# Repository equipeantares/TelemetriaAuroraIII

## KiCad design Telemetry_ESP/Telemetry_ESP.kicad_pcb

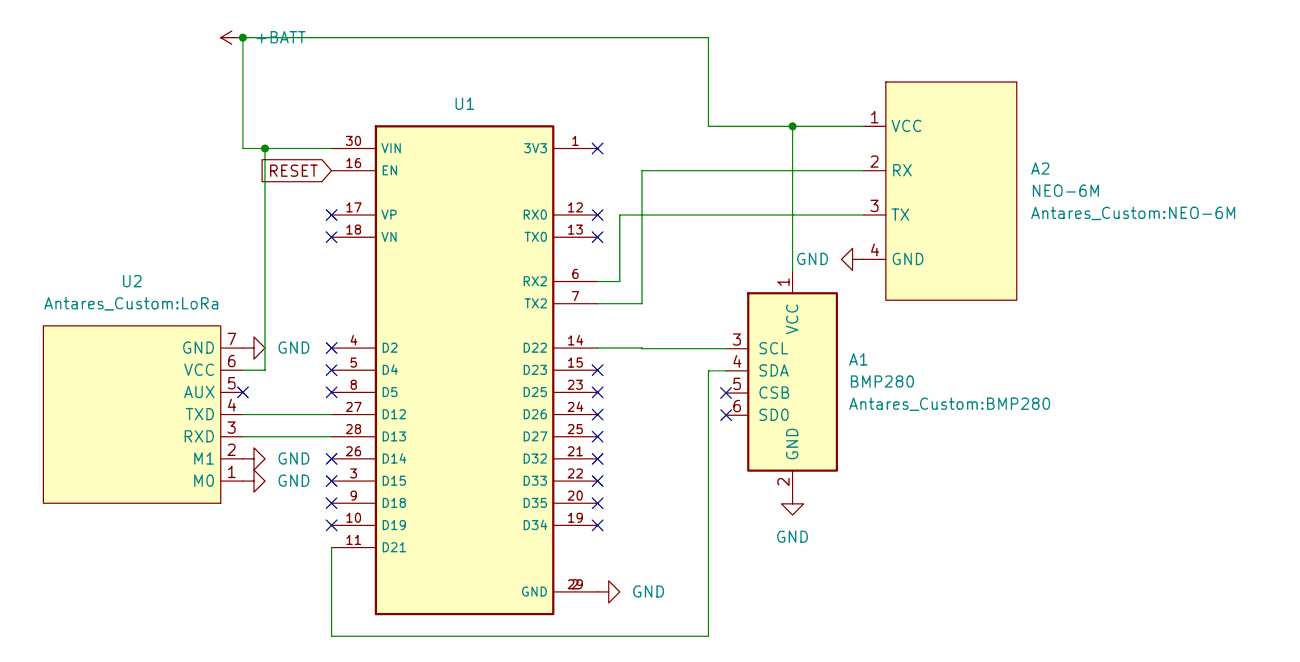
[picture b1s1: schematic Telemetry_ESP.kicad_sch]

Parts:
A1: BMP280
A2: NEO-6M
U1: MODULE_ESP32_DEVKIT_V1
U2: LoRa

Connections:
+BATT: A1.1 (VCC), A2.1 (VCC), U1.30 (VIN), U2.6 (VCC)
GND: A1.2 (GND), A2.4 (GND), U1.2 (GND), U1.29 (GND), U2.1 (M0), U2.2 (M1), U2.7 (GND)
unnamed: A1.3 (SCL), U1.14 (D22)
unnamed: A1.4 (SDA), U1.11 (D21)
unnamed: A2.2 (RX), U1.7 (TX2)
unnamed: A2.3 (TX), U1.6 (RX2)
unnamed: U1.27 (D12), U2.4 (TXD)
unnamed: U1.28 (D13), U2.3 (RXD)
RESET: U1.16 (EN)

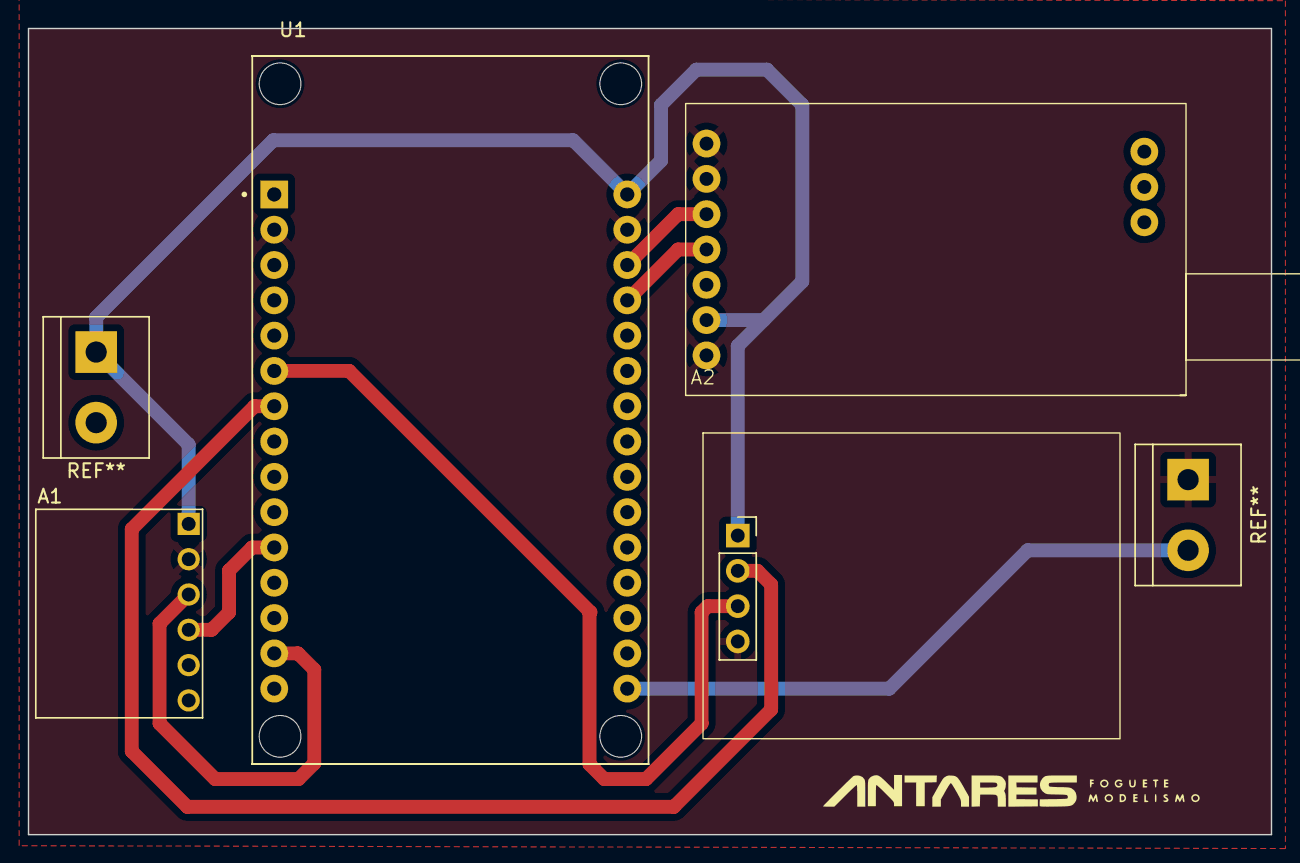
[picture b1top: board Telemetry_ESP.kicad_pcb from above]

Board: 2 copper layers, 89.4 x 58.0 mm, 4 parts (0 on the bottom side), 8 nets.

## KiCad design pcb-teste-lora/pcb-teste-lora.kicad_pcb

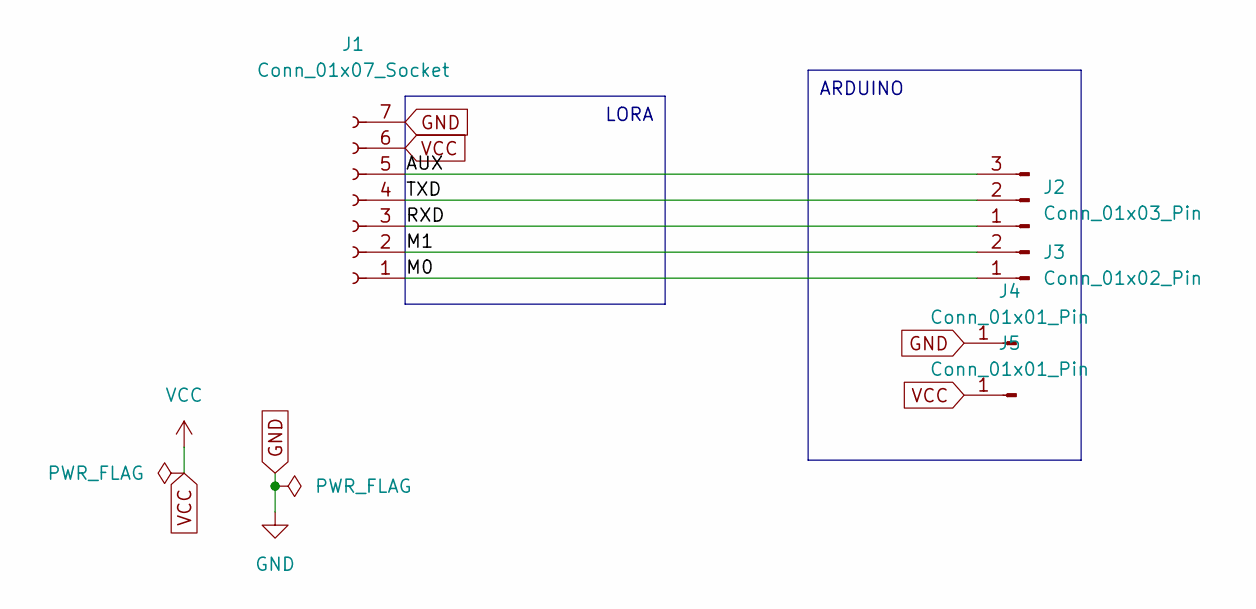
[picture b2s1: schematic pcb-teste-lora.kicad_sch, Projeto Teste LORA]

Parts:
J1: Conn_01x07_Socket; PinSocket_1x07_P2.54mm_Vertical
J2: Conn_01x03_Pin; PinSocket_1x03_P2.54mm_Vertical
J3: Conn_01x02_Pin; PinSocket_1x02_P2.54mm_Vertical
J4, J5: Conn_01x01_Pin; PinSocket_1x01_P2.00mm_Vertical

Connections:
/AUX: J1.5, J2.3
/M0: J1.1, J3.1
/M1: J1.2, J3.2
/RXD: J1.3, J2.1
/TXD: J1.4, J2.2
GND: J1.7, J4.1
VCC: J1.6, J5.1

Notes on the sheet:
LORA
ARDUINO

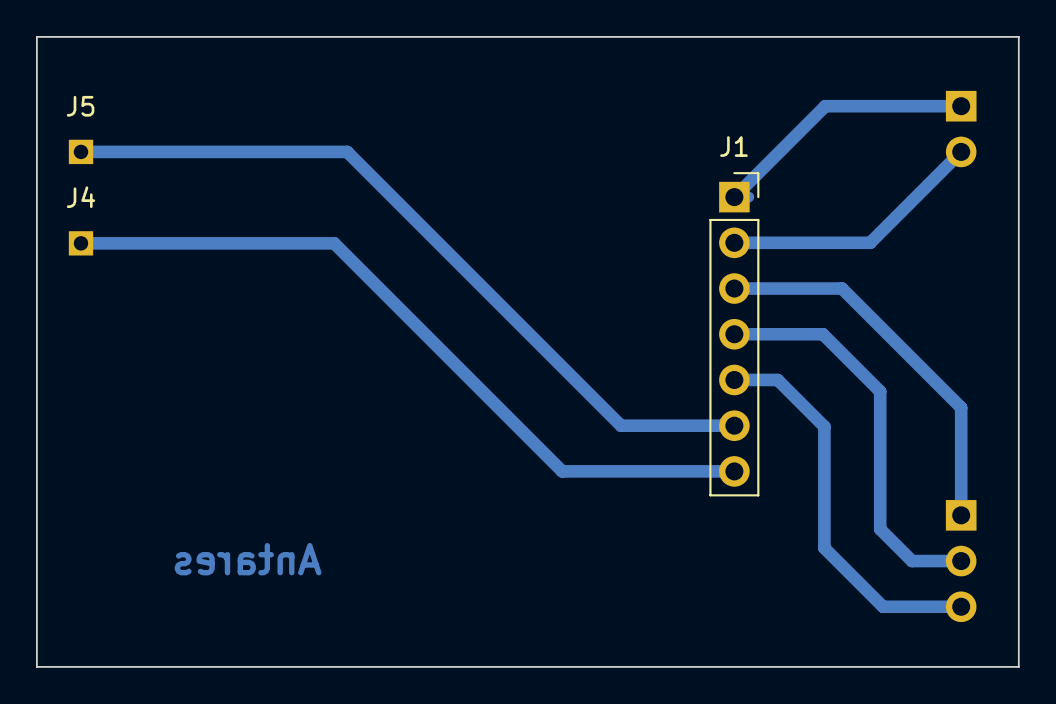
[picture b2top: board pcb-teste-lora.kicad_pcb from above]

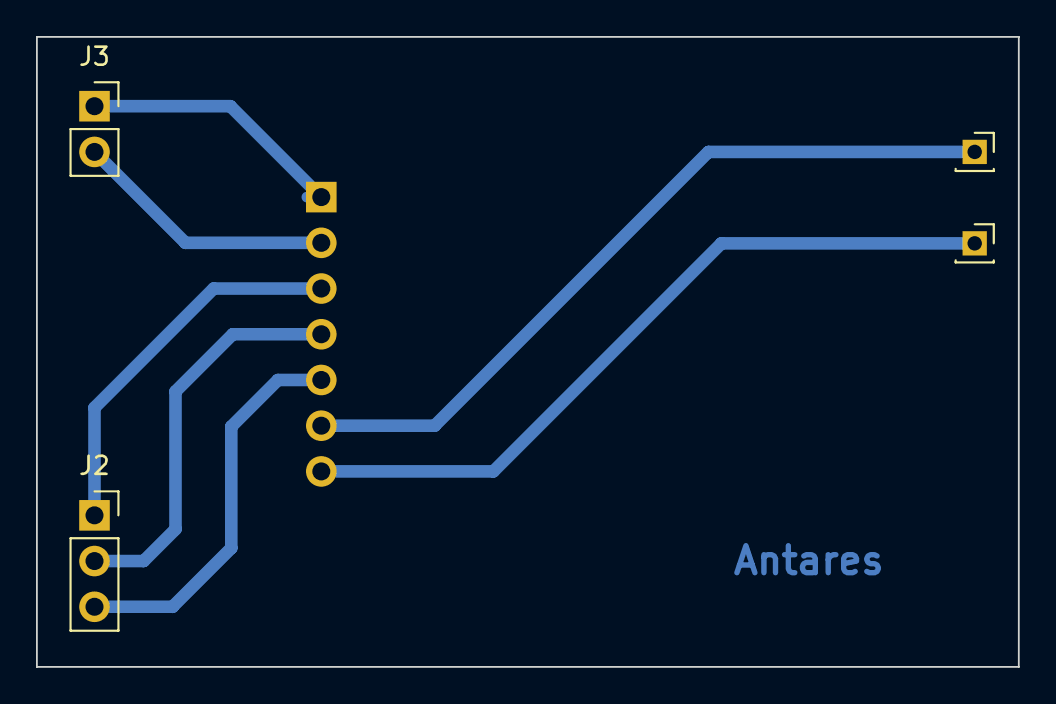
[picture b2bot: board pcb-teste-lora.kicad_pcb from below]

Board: 2 copper layers, 54.5 x 35.0 mm, 5 parts (4 on the bottom side), 7 nets.

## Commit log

2024-03-24 codigo do gsm mais gps do 'Brincando com ideias'
2024-03-27 codigo gsm e gps Brincando com Ideias e Lora
2024-04-12 Arquivo de implementacao lora e gps
2024-04-30 arquivos do lora modificados
2024-06-07 atualizando codigo lora + gps
2024-08-14 Create lora_gps_esp32
2024-09-05 Deletei umas merda e adicionei o código definitivo da telemetria
2024-09-05 deletei umas coisa nada aver
2024-09-10 Added ESP Telemetry
